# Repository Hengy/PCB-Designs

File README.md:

# PCB-Designs
PCB designs for various ICs and circuits, some with frimware examples for testing.

Note: Examples are intended to quickly test functionality of the IC/circuit with fewest external libraries, and may not be the fastest or most effecient.

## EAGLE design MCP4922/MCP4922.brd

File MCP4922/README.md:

# MCP4922 12-bit DAC

This board accomodates two MCP4922 SPI 12-bit DACs, and is intended for high resolution dimming of RGBW high power LED drivers, such as the TPS61169.

The board has serveral options for external voltage reference sources and supply filtering.

# This board is UNTESTED

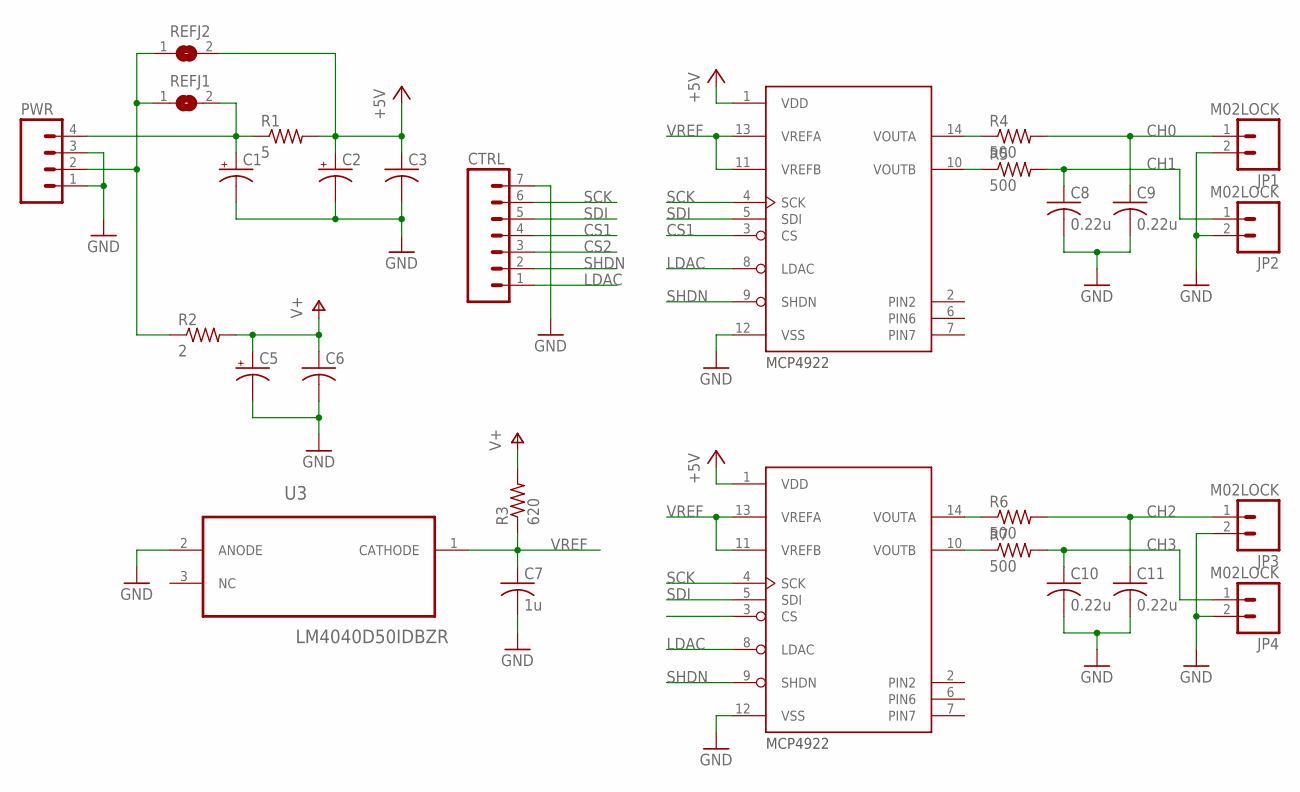
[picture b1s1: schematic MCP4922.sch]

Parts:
C1, C5: CPOL-US153CLV-0405; 153CLV-0405
C2: CPOL-US153CLV-0505; 153CLV-0505
C3, C6: C-USC0805; C0805
C7: 1u; C0805
C8, C9, C10, C11: 0.22u; C0805
CTRL: M07LOCK; 1X07_LOCK
JP1, JP2, JP3, JP4: M02LOCK; 1X02_LOCK
PWR: M04LOCK; 1X04_LOCK
R1: 5; R0805
R2: 2; R0805
R3: 620; R0805
R4, R5, R6, R7: 500; R0805
REFJ1, REFJ2: SJ
U1, U2: MCP4922; SO-14
U3: LM4040D50IDBZR; SOT95P237X112-3N

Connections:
+5V: C2.+, C3.1, R1.2, REFJ2.2, U1.1 (VDD), U2.1 (VDD)
CH0: C9.1, JP1.1, R4.2
CH1: C8.1, JP2.1, R5.2
CH2: C11.1, JP3.1, R6.2
CH3: C10.1, JP4.1, R7.2
CS1: CTRL.4, U1.3 (CS)
CS2: CTRL.3, U2.3 (CS)
GND: C1.-, C2.-, C3.2, C5.-, C6.2, C7.2, C8.2, C9.2, C10.2, C11.2, CTRL.7, JP1.2, JP2.2, JP3.2, JP4.2, PWR.1, PWR.3, U1.12 (VSS), U2.12 (VSS), U3.2 (ANODE)
LDAC: CTRL.1, U1.8 (LDAC), U2.8 (LDAC)
unnamed: R7.1, U2.10 (VOUTB)
unnamed: R6.1, U2.14 (VOUTA)
unnamed: R5.1, U1.10 (VOUTB)
unnamed: R4.1, U1.14 (VOUTA)
unnamed: C1.+, PWR.4, R1.1, REFJ1.2
unnamed: PWR.2, R2.1, REFJ1.1, REFJ2.1
SCK: CTRL.6, U1.4 (SCK), U2.4 (SCK)
SDI: CTRL.5, U1.5 (SDI), U2.5 (SDI)
SHDN: CTRL.2, U1.9 (SHDN), U2.9 (SHDN)
V+: C5.+, C6.1, R2.2, R3.2
VREF: C7.1, R3.1, U1.11 (VREFB), U1.13 (VREFA), U2.11 (VREFB), U2.13 (VREFA), U3.1 (CATHODE)

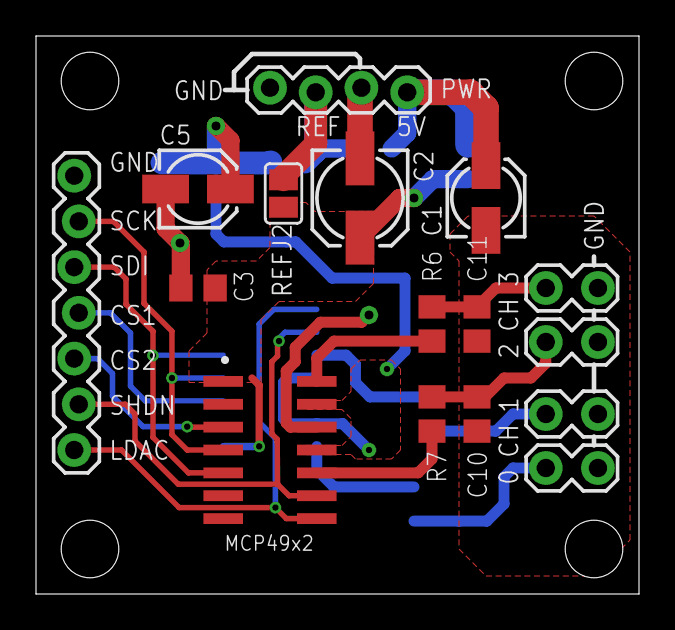
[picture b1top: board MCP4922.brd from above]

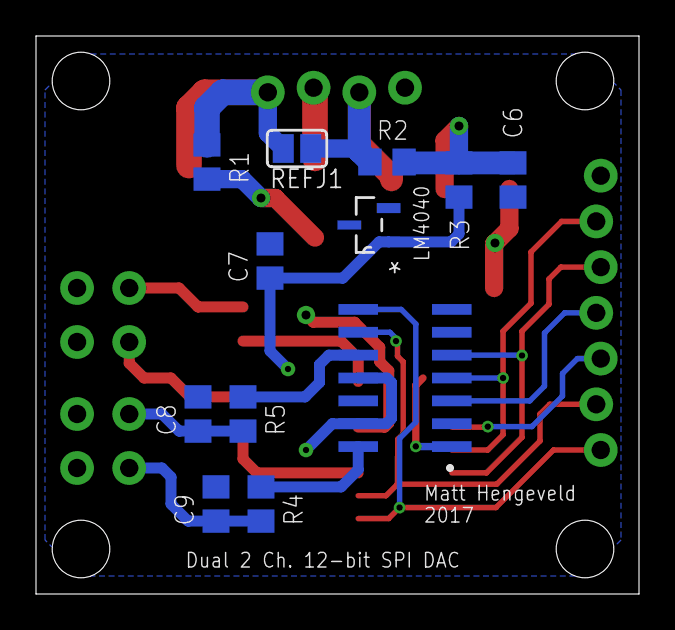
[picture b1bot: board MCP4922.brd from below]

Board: 2 copper layers, 33.5 x 31.0 mm, 28 parts (12 on the bottom side), 20 nets.

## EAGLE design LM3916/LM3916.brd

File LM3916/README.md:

# LM3914/5/6

Designed to use the LM3916 (but can use the LM3914/5) to make a LED VU meter.

Op amp on input should be a rail-to-rail type (NOT a NE5532 as originally silkscreened, and as used in the schematic). Rail-torail op amps that are pin compatible include the TLC2272 and the TL972, but there are many others. The TLC2272 is cheap. Noise performance shouldn't be an issue with an LED output.

The op amp / trimmer combo is meant to amplify the typical 0.7-1.2V line level from standard consumer audio equipment to the full range of the LM3916, with the trimmer used to adjust for different input voltages and op amp gains.

Using R28 = 2K, and R29 = 3.3K, gives a full range of approx. 0-3.8V, with an LED current of aobut 9.7mA.

For my application, I used R25 = 10k, and R26 = 680, which gives the op amp a gain of approx. 15.7. This, with an input amplitude of 250mV, gives 3.925. The trimmer is then used to reduce the voltage to within the 0-3.8V range.

The tutorial here: https://learn.sparkfun.com/tutorials/dotbar-display-driver-hookup-guide is a really good guide to calculating resistor values.

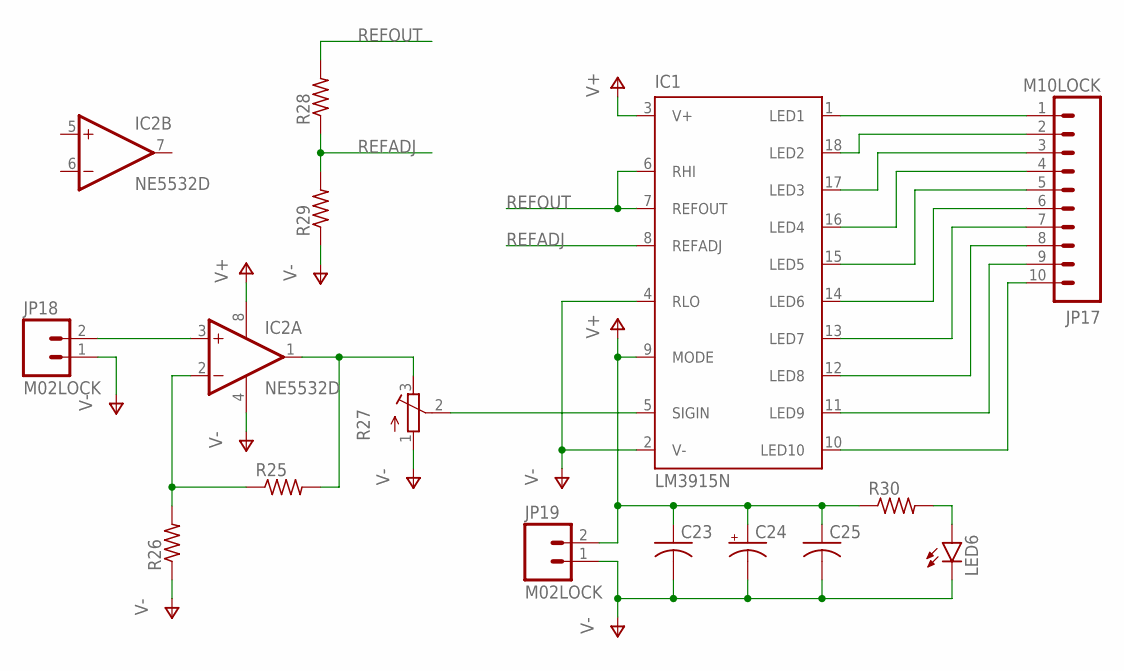
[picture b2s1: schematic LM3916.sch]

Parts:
C23, C25: C-USC0805; C0805
C24: CPOL-USE2-5; E2-5
IC1: LM3915N; DIL18
IC2: NE5532D; SO08
JP17: M10LOCK; 1X10_LOCK
JP18, JP19: M02LOCK; 1X02_LOCK
LED6: LED1206; LED-1206
R25, R26, R28, R29, R30: R-US_R0805; R0805
R27: R-TRIMM64W; RTRIM64W

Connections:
unnamed: IC1.1 (LED1), JP17.1
unnamed: IC1.18 (LED2), JP17.2
unnamed: IC1.17 (LED3), JP17.3
unnamed: IC1.16 (LED4), JP17.4
unnamed: IC1.15 (LED5), JP17.5
unnamed: IC1.14 (LED6), JP17.6
unnamed: IC1.13 (LED7), JP17.7
unnamed: IC1.12 (LED8), JP17.8
unnamed: IC1.11 (LED9), JP17.9
unnamed: IC1.10 (LED10), JP17.10
unnamed: IC2.2 (-IN), R25.1, R26.2
unnamed: IC2.1 (OUT), R25.2, R27.3 (E)
unnamed: LED6.A, R30.2
unnamed: IC2.3 (+IN), JP18.2
unnamed: IC1.5 (SIGIN), R27.2 (S)
REFADJ: IC1.8 (REFADJ), R28.1, R29.2
REFOUT: IC1.6 (RHI), IC1.7 (REFOUT), R28.2
V+: C23.1, C24.+, C25.1, IC1.3 (V+), IC1.9 (MODE), IC2.8 (V+), JP19.2, R30.1
V-: C23.2, C24.-, C25.2, IC1.2 (V-), IC1.4 (RLO), IC2.4 (V-), JP18.1, JP19.1, LED6.C, R26.1, R27.1 (A), R29.1

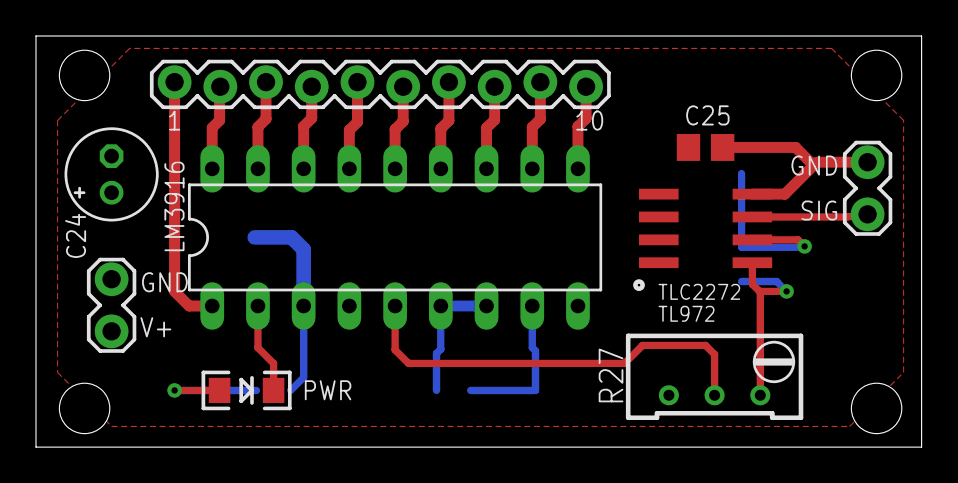
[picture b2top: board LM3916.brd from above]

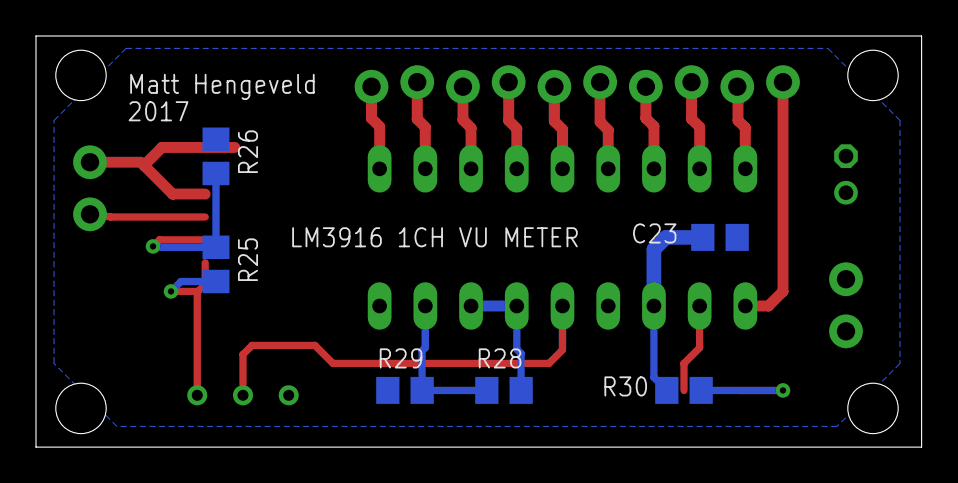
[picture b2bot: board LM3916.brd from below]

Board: 2 copper layers, 49.2 x 22.8 mm, 15 parts (6 on the bottom side), 19 nets.

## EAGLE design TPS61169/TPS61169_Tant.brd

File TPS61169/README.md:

# TPS61169 LED Driver

There are three different PCB designs for the TPS61169.

The power supply used plays a large role in the ability of this driver to drive LEDs. It must be capable of sourcing 2-4x the LED output current, and be able to handle large transients typical of a boost converter.

Note: the max input voltage of the TPS61169 is 5.5V!

TPS61169_Tant is the smallest layout, and uses a tantalum capacitor on the input. This is suitable for driving small LED loads (up to 200mA, ~20V).

TPS61169_El uses a electrolytic capacitor on the input. This is suitable for small to moderate LED loads (up to 350mA, ~24V). The electrolytic cap should be greater than 330uF, and low ESR.

L1 is 4.7-10uH, CD54 package, and should be rated for 2-3x the LED current. There are two footprints in the PCB, one for SMD, and one for through hole.

C3, C4 should be 1-2.2uF, 1206 package, X7R or better, and rated for greater than twice the LED voltage.

R2-R5 allow for parallel feedback resistors. This makes it easier, and sometimes less expensive to get the correct feedback resistance for a given LED current.

D1 should be a Schottky diode, rated for greater than the LED voltage, and greater than the output current.

Output capability of the above two designs can be increased by putting more capacitance on the input.

TPS61169_HPLED is a larger PCB design with a larger inductor footprint (DR125 package) and two electrolytic input capacitors. This is suitable for getting driving high power LEDs from the TPS61169 (up to 750mA, 38V). 

Note: I have not tested the TPS61169 at greater than 500mA, ~24V output.

PWM Dimming:

The TPS61169 uses PWM on the CTRL pin to impliment dimming. The datasheet states a minimum of 5KHz PWM frequency. My own tests using the TLC5973 with a PWM frequency of ~3KHz to be adaquate in the range of 5-100% duty cycle, however, the first 5% is poor, turning on the LEDs fairly brightly even at 0.5% duty. Using a >5KHz PWM frequency may have better results.

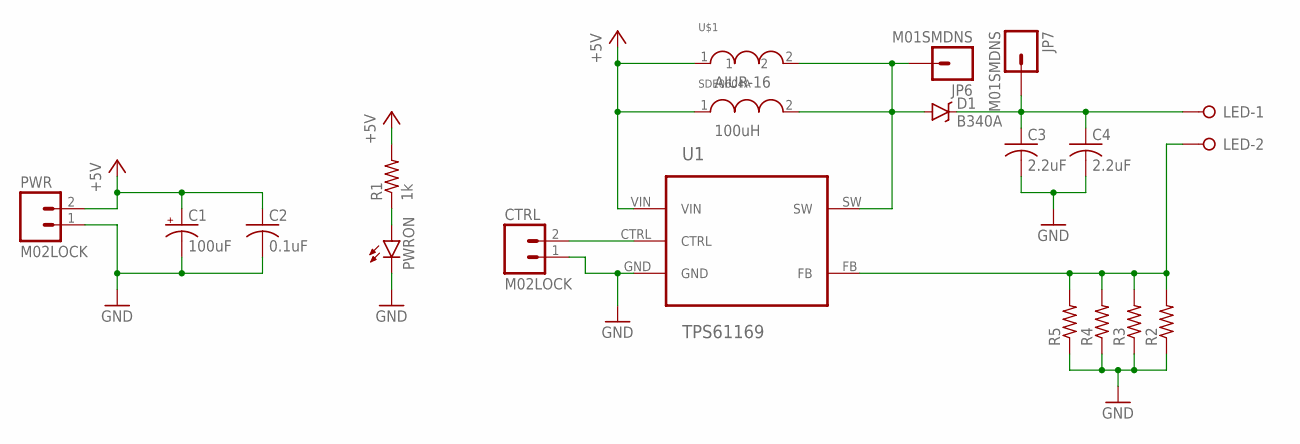
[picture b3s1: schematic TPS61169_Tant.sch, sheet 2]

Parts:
AIUR-16: 100uH; 3MM_LEADS_7MM
C1: 100uF; SMC_C
C2: 0.1uF; C0805
C3, C4: 2.2uF; C0805
CTRL: M02LOCK; 1X02_LOCK
D1: B340A; SMA-DIODE
JP6, JP7: M01SMDNS; 1X01NS
LED: W237-02P; W237-132
PWR: M02LOCK; 1X02_LOCK
PWRON: LED1206; LED-1206
R1: 1k; R0805
R2, R3, R4, R5: R-US_R0805; R0805
U1: TPS61169; SOT65P210X110-5N
U$1: SDE0604A; BOURNS_SMD

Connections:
+5V: AIUR-16.1, C1.+, C2.1, PWR.2, R1.2, U1.VIN, U$1.1
GND: C1.-, C2.2, C3.2, C4.2, CTRL.1, PWR.1, PWRON.C, R2.1, R3.1, R4.1, R5.1, U1.GND
unnamed: CTRL.2, U1.CTRL
unnamed: AIUR-16.2, D1.A, JP6.1, U1.SW, U$1.2
unnamed: LED.2, R2.2, R3.2, R4.2, R5.2, U1.FB
unnamed: C3.1, C4.1, D1.C, JP7.1, LED.1
unnamed: PWRON.A, R1.1

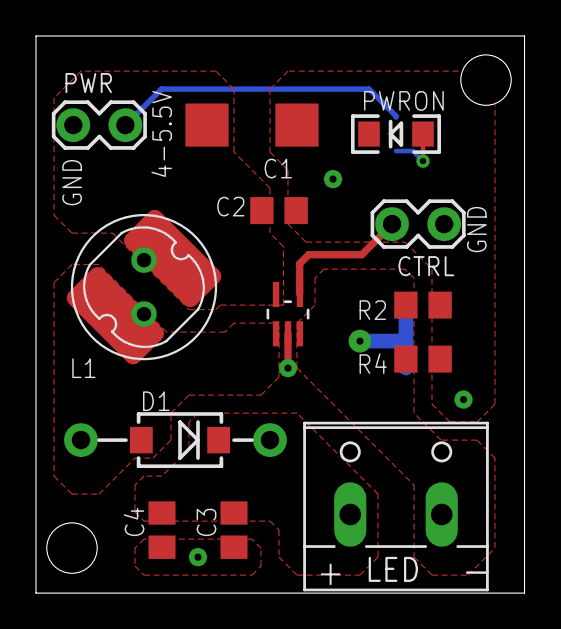
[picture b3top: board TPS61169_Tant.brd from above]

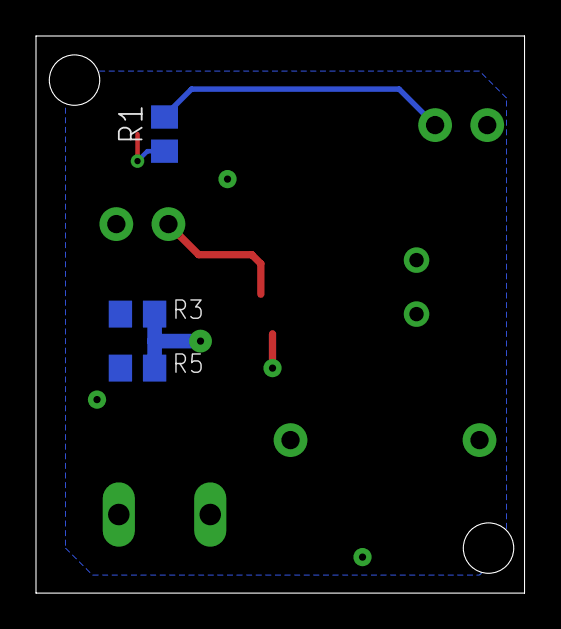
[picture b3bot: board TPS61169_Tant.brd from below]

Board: 2 copper layers, 27.1 x 30.9 mm, 19 parts (3 on the bottom side), 7 nets.

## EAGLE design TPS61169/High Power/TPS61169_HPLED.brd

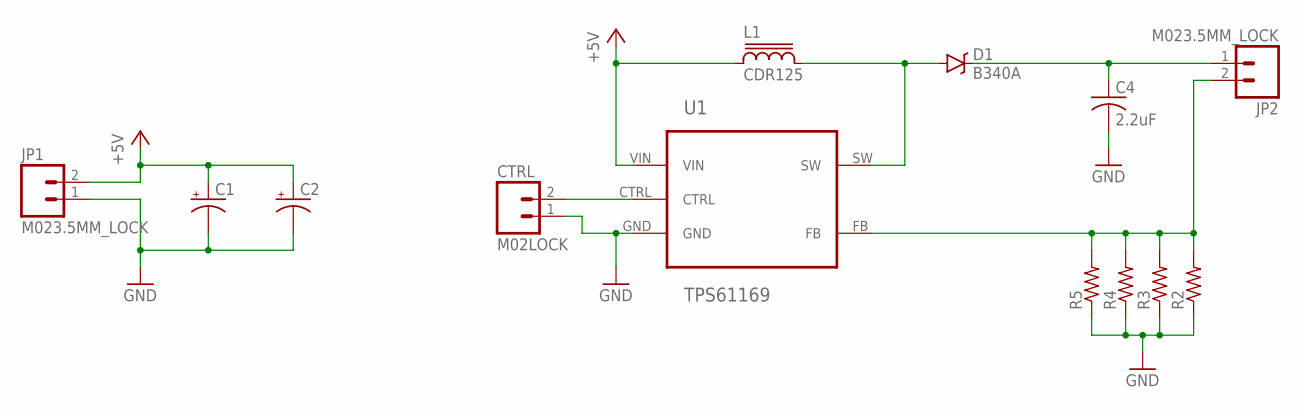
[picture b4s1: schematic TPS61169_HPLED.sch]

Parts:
C1, C2: CPOL-USE3.5-8; E3,5-8
C4: 2.2uF; C0805
CTRL: M02LOCK; 1X02_LOCK
D1: B340A; SMA-DIODE
JP1, JP2: M023.5MM_LOCK; SCREWTERMINAL-3.5MM-2_LOCK
L1: CDR125
R2, R3, R4, R5: R-US_R0805; R0805
U1: TPS61169; SOT65P210X110-5N

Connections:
+5V: C1.+, C2.+, JP1.2, L1.1, U1.VIN
GND: C1.-, C2.-, C4.2, CTRL.1, JP1.1, R2.1, R3.1, R4.1, R5.1, U1.GND
unnamed: CTRL.2, U1.CTRL
unnamed: D1.A, L1.2, U1.SW
unnamed: JP2.2, R2.2, R3.2, R4.2, R5.2, U1.FB
unnamed: C4.1, D1.C, JP2.1

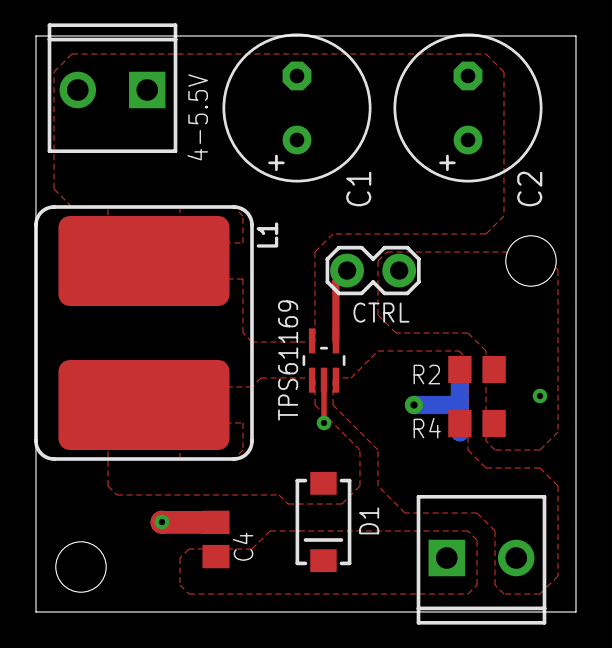
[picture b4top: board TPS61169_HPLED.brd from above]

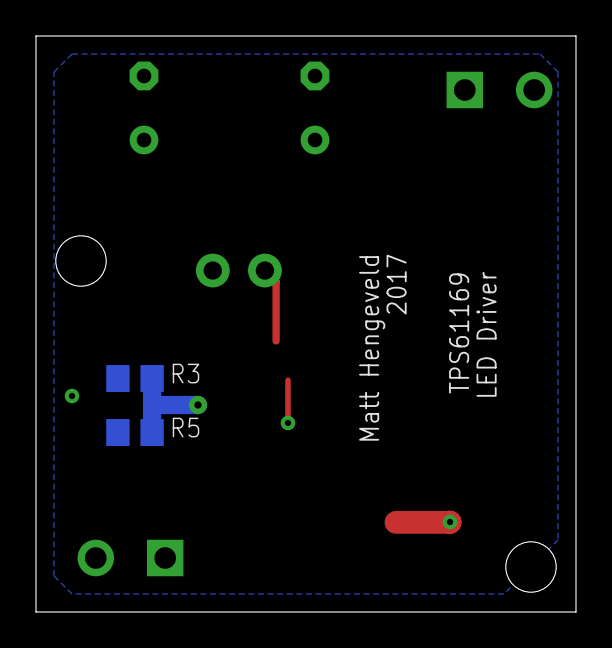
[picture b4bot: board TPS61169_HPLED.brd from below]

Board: 2 copper layers, 30.0 x 32.0 mm, 13 parts (2 on the bottom side), 6 nets.

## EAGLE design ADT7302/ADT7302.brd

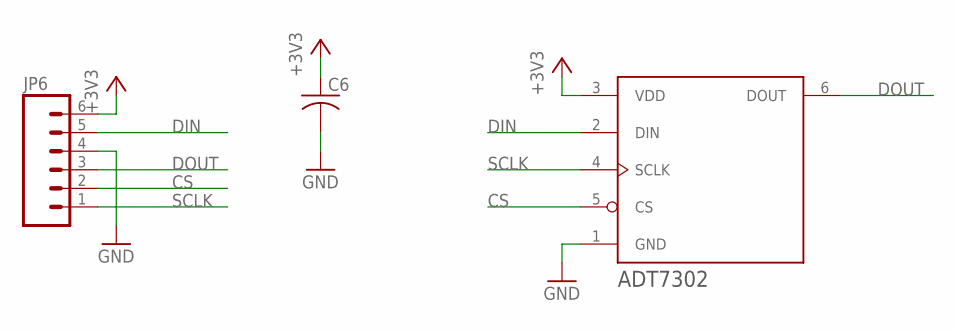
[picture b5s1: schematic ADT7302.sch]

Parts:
C6: C-USC0805K; C0805K
JP6: M06LOCK; 1X06_LOCK
U$2: ADT7302; SOT23

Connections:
+3V3: C6.1, JP6.6, U$2.3 (VDD)
CS: JP6.2, U$2.5 (CS)
DIN: JP6.5, U$2.2 (DIN)
DOUT: JP6.3, U$2.6 (DOUT)
GND: C6.2, JP6.4, U$2.1 (GND)
SCLK: JP6.1, U$2.4 (SCLK)

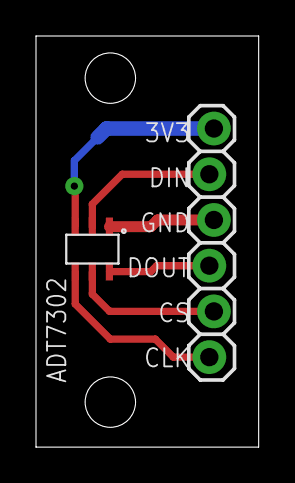
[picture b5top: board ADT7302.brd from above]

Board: 2 copper layers, 12.4 x 22.8 mm, 3 parts (1 on the bottom side), 6 nets.

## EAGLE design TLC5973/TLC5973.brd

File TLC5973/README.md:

# TLC5973

This PCB was designed to control brightness for LED drivers - that is, it provides 3 channels of non-inverted 12-bit PWM.

Since the TLC5973 has current sink outputs, the PWM signal is inverted. The output transistor will invert the signal again, resulting in a non-inverted output.

R1 sets output current. For driving the BJTs, 35mA is sufficient.

R3-R5 should be sized to provide all output current to the BJTs base. I used 100 Ohms.

R6-R8 should be 10K Ohms.

Q1-Q3 are SOT23-3 PNP BJT transistors.

This can be run on 3.3V, but output current is limited.

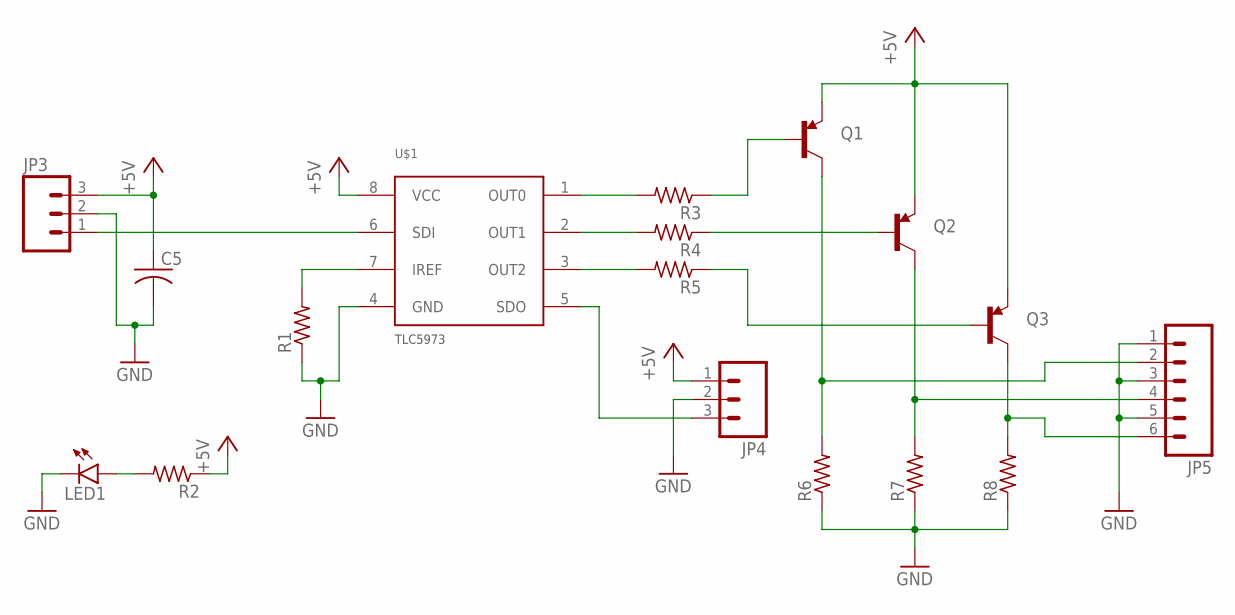
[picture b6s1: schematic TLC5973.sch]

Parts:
C5: C-USC0805K; C0805K
JP3, JP4: M03LOCK; 1X03_LOCK
JP5: M06LOCK; 1X06_LOCK
LED1: LED1206; LED-1206
Q1, Q2, Q3: TRANSISTOR_PNPSMD; SOT23-3
R1, R2, R3, R4, R5, R6, R7, R8: R-US_R0805; R0805
U$1: TLC5973; SO-08

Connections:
+5V: C5.1, JP3.3, JP4.1, Q1.2 (E), Q2.2 (E), Q3.2 (E), R2.1, U$1.8 (VCC)
GND: C5.2, JP3.2, JP4.2, JP5.1, JP5.3, JP5.5, LED1.C, R1.1, R6.1, R7.1, R8.1, U$1.4 (GND)
unnamed: R1.2, U$1.7 (IREF)
unnamed: JP3.1, U$1.6 (SDI)
unnamed: Q2.1 (B), R4.1
unnamed: Q1.1 (B), R3.1
unnamed: Q3.1 (B), R5.1
unnamed: JP4.3, U$1.5 (SDO)
unnamed: LED1.A, R2.2
unnamed: JP5.2, Q1.3 (C), R6.2
unnamed: R3.2, U$1.1 (OUT0)
unnamed: R4.2, U$1.2 (OUT1)
unnamed: R5.2, U$1.3 (OUT2)
unnamed: JP5.4, Q2.3 (C), R7.2
unnamed: JP5.6, Q3.3 (C), R8.2

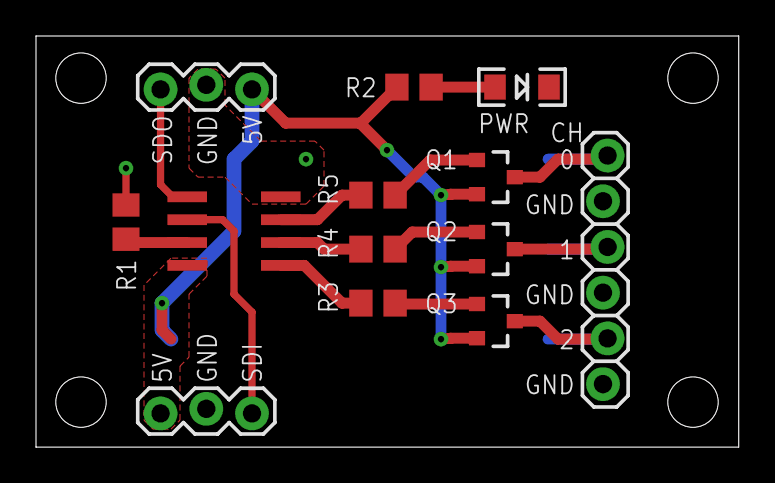
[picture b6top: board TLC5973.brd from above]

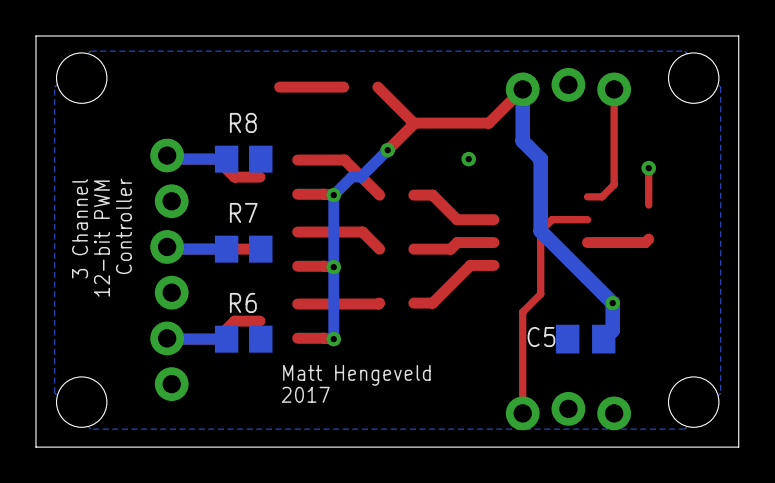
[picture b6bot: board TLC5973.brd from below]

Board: 2 copper layers, 39.0 x 22.8 mm, 17 parts (4 on the bottom side), 15 nets.

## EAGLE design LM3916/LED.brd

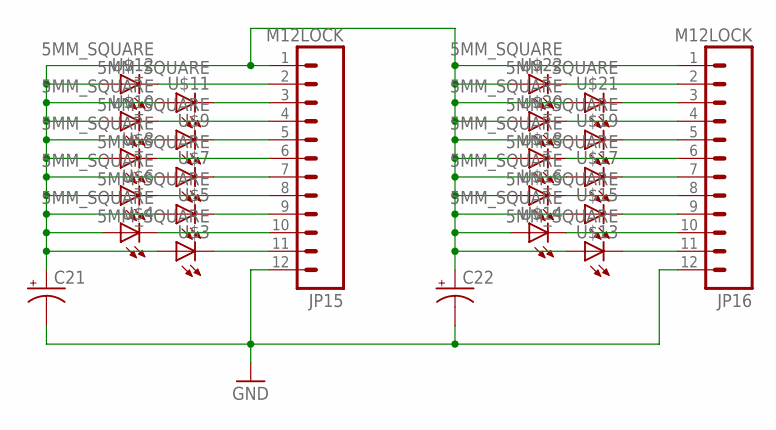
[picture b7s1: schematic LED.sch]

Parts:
C21, C22: CPOL-USE2-5; E2-5
JP15, JP16: M12LOCK; 1X12_LOCK
U$3, U$4, U$5, U$6, U$7, U$8, U$9, U$10, U$11, U$12, U$13, U$14, U$15, U$16, U$17, U$18, U$19, U$20, U$21, U$22: 5MM_SQUARE

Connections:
GND: C21.-, C22.-, JP15.12, JP16.12
unnamed: JP16.2, U$22.N (C)
unnamed: JP16.3, U$21.N (C)
unnamed: JP16.4, U$20.N (C)
unnamed: JP16.5, U$19.N (C)
unnamed: JP16.6, U$18.N (C)
unnamed: JP16.7, U$17.N (C)
unnamed: JP16.8, U$16.N (C)
unnamed: JP16.9, U$15.N (C)
unnamed: C21.+, C22.+, JP15.1, JP16.1, U$3.P (A), U$4.P (A), U$5.P (A), U$6.P (A), U$7.P (A), U$8.P (A), U$9.P (A), U$10.P (A), U$11.P (A), U$12.P (A), U$13.P (A), U$14.P (A), U$15.P (A), U$16.P (A), U$17.P (A), U$18.P (A), U$19.P (A), U$20.P (A), U$21.P (A), U$22.P (A)
unnamed: JP15.2, U$12.N (C)
unnamed: JP15.3, U$11.N (C)
unnamed: JP15.4, U$10.N (C)
unnamed: JP15.5, U$9.N (C)
unnamed: JP15.6, U$8.N (C)
unnamed: JP15.7, U$7.N (C)
unnamed: JP15.8, U$6.N (C)
unnamed: JP15.9, U$5.N (C)
unnamed: JP15.10, U$4.N (C)
unnamed: JP15.11, U$3.N (C)
unnamed: JP16.10, U$14.N (C)
unnamed: JP16.11, U$13.N (C)

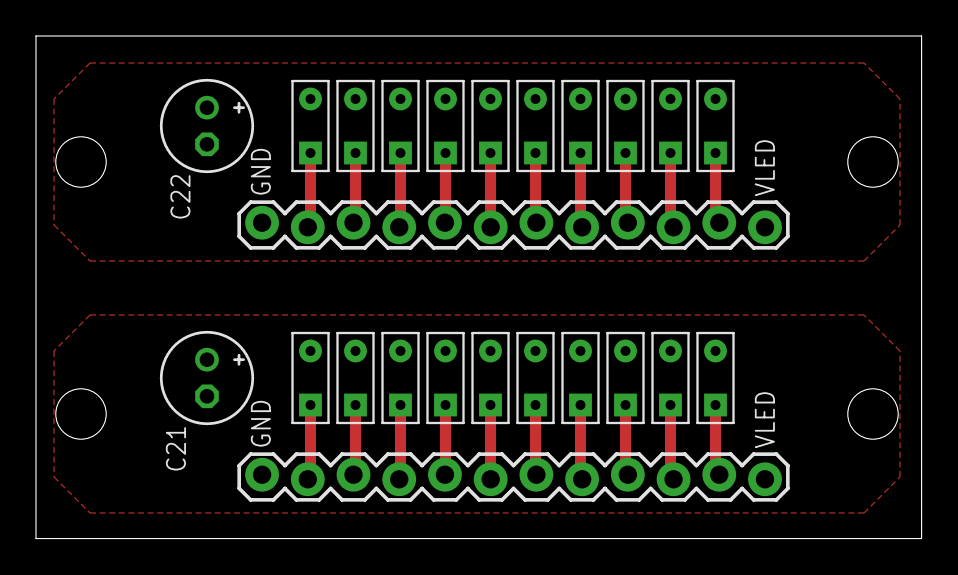
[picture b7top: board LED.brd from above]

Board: 2 copper layers, 49.2 x 27.9 mm, 24 parts (0 on the bottom side), 22 nets.

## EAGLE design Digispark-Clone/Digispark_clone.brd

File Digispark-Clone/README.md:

# Digispark Clone

This was designed to use the Digispark bootloader, and drive WS2812/SK6812 addressable LEDs.

R20 & R21 are 68 Ohms 0805.

Uses USB Mini connector.

Sensor Connect jumper is designed to allow programming with USB without removing a sensor connected to PB4 (USB D+)

Uses ATtiny85.

Note: Programming process is somewhat complicated. First program must be with a AVR ISP. It is recommended to first program the Micronucleus bootloader version with Reset (PB5) enabled. This allows it to be programmed again using ISP. If successful, one can then program the version with Reset disabled for an extra I/O pin.
Nothing can be connected to USB D+/D- (PB4/PB5) while programming using USB. Some computers will not recognize this as a USB device because of the lack of Zener diodes on the data lines. A USB hub is recommended for extra protection/compatability.

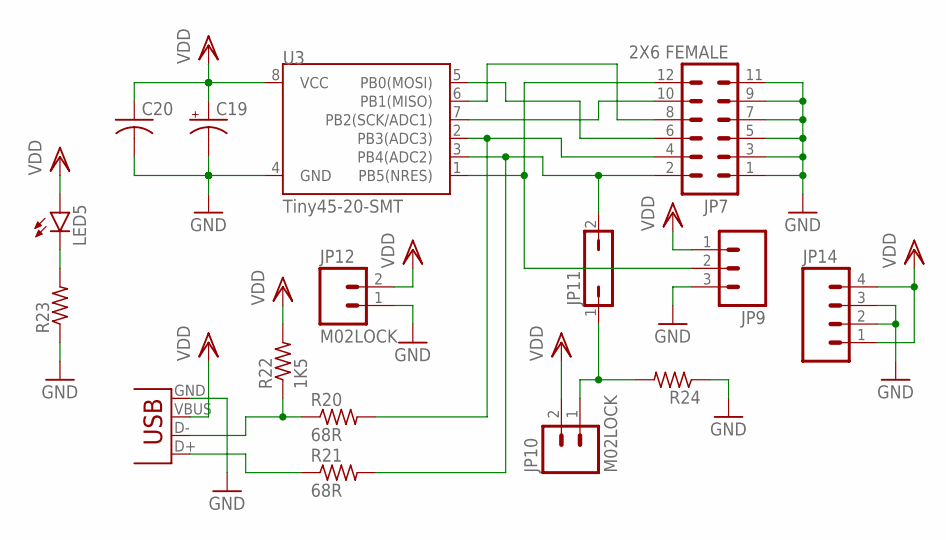
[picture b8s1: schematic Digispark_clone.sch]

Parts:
C19: CPOL-USE2-5; E2-5
C20: C-USC0805; C0805
JP7: 2X6 FEMALE; 2X6
JP8: USB-SMD-NS; USB-MINIB-NOSTOP
JP9: M03LOCK; 1X03_LOCK
JP10, JP12: M02LOCK; 1X02_LOCK
JP11: JP1Q; JP1
JP14: M04LOCK; 1X04_LOCK
LED5: LED1206; LED-1206
R20, R21: 68R; R0805
R22: 1K5; R0805
R23, R24: R-US_R0805; R0805
U3: Tiny45-20-SMT; SO08-EIAJ

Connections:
D+: JP7.2, JP11.2, R21.2, U3.3 (PB4(ADC2))
D-: JP7.4, R20.2, U3.2 (PB3(ADC3))
GND: C19.-, C20.2, JP7.1, JP7.3, JP7.5, JP7.7, JP7.9, JP7.11, JP8.GND, JP9.3, JP12.1, JP14.2, JP14.3, R23.1, R24.1, U3.4 (GND)
unnamed: JP7.12, JP9.2, U3.1 (PB5(NRES))
unnamed: JP7.6, U3.5 (PB0(MOSI))
unnamed: JP7.10, U3.7 (PB2(SCK/ADC1))
unnamed: JP10.1, JP11.1, R24.2
unnamed: JP7.8, U3.6 (PB1(MISO))
unnamed: LED5.C, R23.2
unnamed: JP8.D-, R20.1, R22.1
unnamed: JP8.D+, R21.1
VDD: C19.+, C20.1, JP8.VBUS, JP9.1, JP10.2, JP12.2, JP14.1, JP14.4, LED5.A, R22.2, U3.8 (VCC)

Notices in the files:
parts and their libraries:
SparkFun-Connectors: Licensing: Creative Commons ShareAlike 4.0 International - https://creativecommons.org/licenses/by-sa/4.0
inductor-sumida: Copyright (C) 2008, Bob Starr
